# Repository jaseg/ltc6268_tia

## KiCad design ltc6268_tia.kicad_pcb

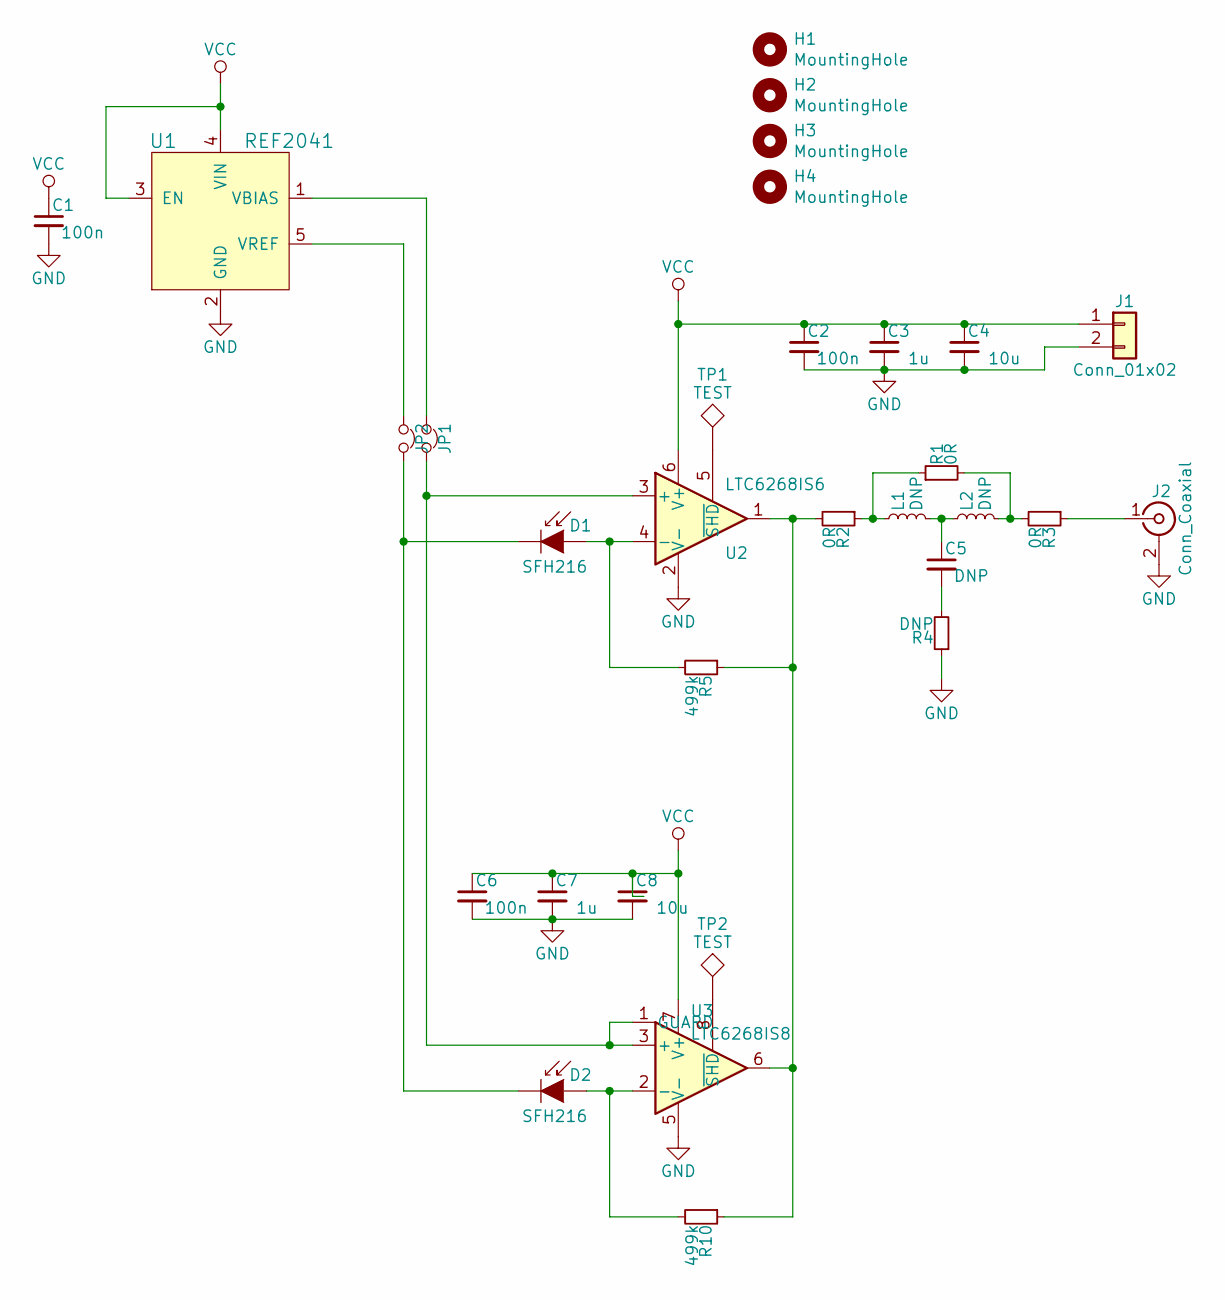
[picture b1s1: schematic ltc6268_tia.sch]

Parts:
C1, C2, C6: 100n; C_0402_1005Metric
C3, C7: 1u; C_0603_1608Metric_Pad1.05x0.95mm_HandSolder
C4, C8: 10u; C_0603_1608Metric_Pad1.05x0.95mm_HandSolder
C5: DNP; C_0402_1005Metric
D1, D2: SFH216; LED_1206_3216Metric
H1, H2, H3, H4: MountingHole; MountingHole_3.2mm_M3
J1: Conn_01x02; PhoenixContact_MC_1,5_2-G-5.08_1x02_P5.08mm_Horizontal
J2: Conn_Coaxial; SMA_Amphenol_132289_EdgeMount
JP1, JP2: Jumper_NC_Small; SolderJumper-2_P1.3mm_Open_RoundedPad1.0x1.5mm
L1, L2: DNP; L_0603_1608Metric_Pad1.05x0.95mm_HandSolder
R1, R2, R3: 0R; R_0402_1005Metric
R4: DNP; R_0402_1005Metric
R5, R10: 499k; R_0402_1005Metric
TP1, TP2: TEST; TestPoint_Pad_D1.5mm
U1: REF2041; SOT-23-5_HandSoldering
U2: LTC6268IS6; SOT-23-6
U3: LTC6268IS8; SO-8_3.9x4.9mm_P1.27mm

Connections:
GND: C1.2, C2.2, C3.2, C4.2, C6.2, C7.2, C8.2, J1.2, J2.2 (Ext), R4.1, U1.2 (GND), U2.2 (V-), U3.5 (V-)
unnamed: C5.1, L1.2, L2.1
unnamed: C5.2, R4.2
unnamed: D1.1 (K), D2.1 (K), JP2.2
unnamed: D1.2 (A), R5.2, U2.4 (-)
unnamed: D2.2 (A), R10.2, U3.2 (-)
unnamed: J2.1 (In), R3.1
unnamed: JP1.1, U1.1 (VBIAS)
unnamed: JP1.2, U2.3 (+), U3.1 (GUARD), U3.3 (+)
unnamed: JP2.1, U1.5 (VREF)
unnamed: L1.1, R1.1, R2.1
unnamed: L2.2, R1.2, R3.2
unnamed: R2.2, R5.1, R10.1, U2.1, U3.6
unnamed: TP1.1, U2.5 (~SHD)
unnamed: TP2.1, U3.8 (~SHD)
VCC: C1.1, C2.1, C3.1, C4.1, C6.1, C7.1, C8.1, J1.1, U1.3 (EN), U1.4 (VIN), U2.6 (V+), U3.7 (V+)

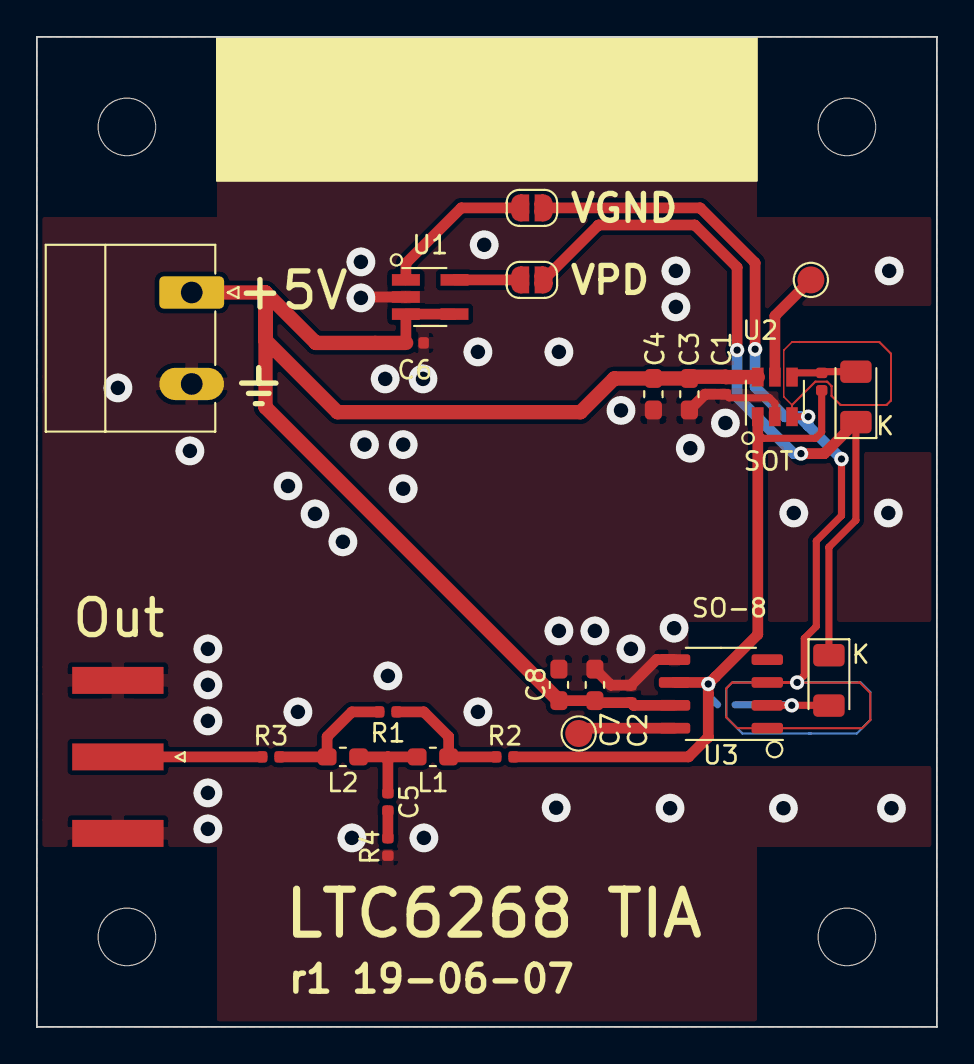
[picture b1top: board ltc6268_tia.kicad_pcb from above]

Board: 2 copper layers, 50.0 x 55.0 mm, 31 parts (1 on the bottom side), 16 nets.
